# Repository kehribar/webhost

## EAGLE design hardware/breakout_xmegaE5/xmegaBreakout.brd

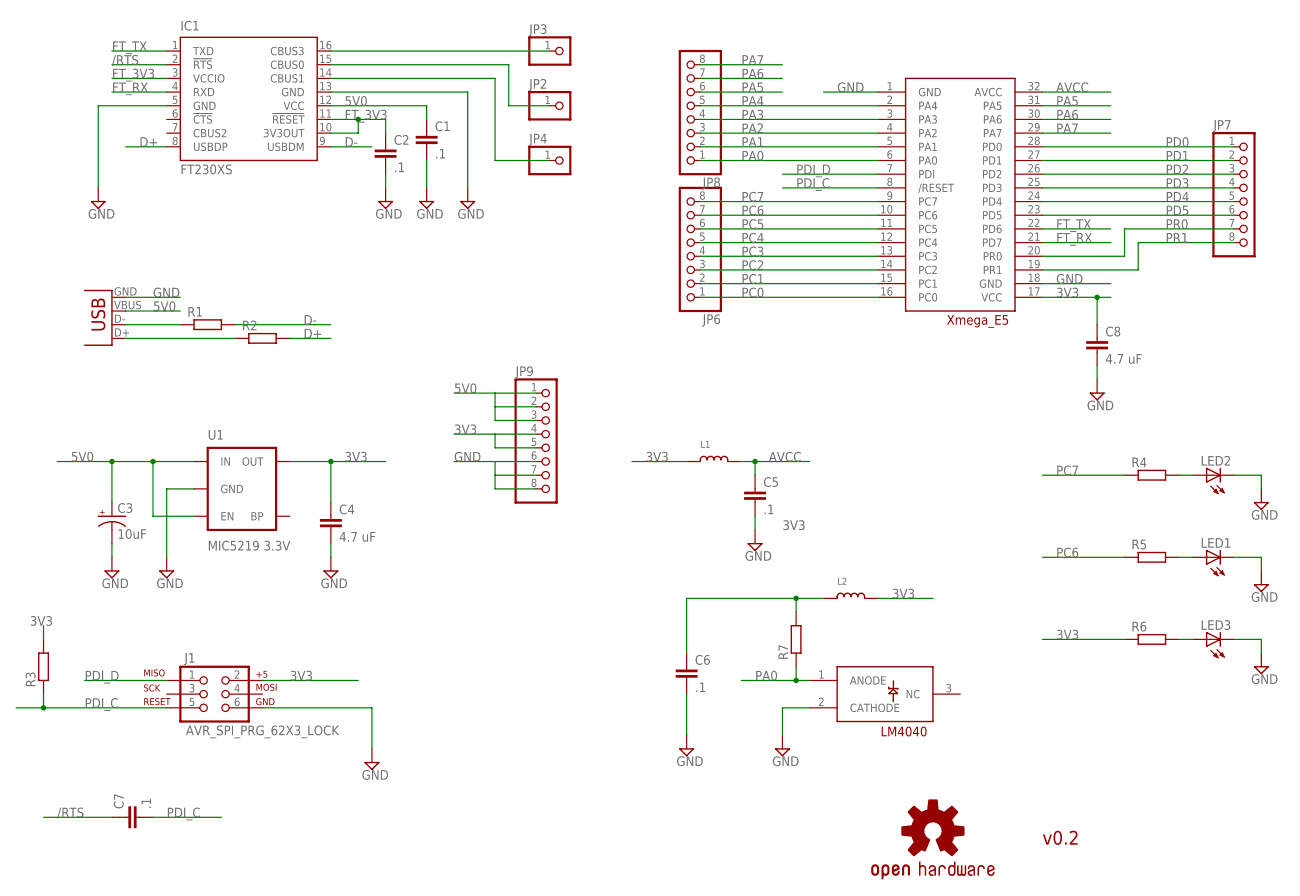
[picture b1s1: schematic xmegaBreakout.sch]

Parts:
C1, C2, C5, C6, C7: .1; C0603
C3: 10uF; EIA3216
C4, C8: 4.7 uF; C0603
IC1: FT230XS; SSOP16
J1: AVR_SPI_PRG_62X3_LOCK; 2X3_LOCK
JP1: USBOLD; USB-MINIB-OLD
JP2, JP3, JP4: HEADER-1X1ROUND; 1X01_ROUND
JP6, JP7, JP8, JP9: HEADER-1X8ROUND; 1X08_ROUND
L1, L2: INDUCTOR0805; 0805
LED1, LED2, LED3: LED0603; LED-0603
LOGO1: OSHW-LOGOS; OSHW-LOGO-S
R1, R2, R3, R4, R5, R6, R7: R-EU_R0603; R0603
U1: MIC5219 3.3V; SOT23-5
U$1: IHSAN_XMEGA_E5; TQFP32-08
U$2: IHSAN_LM4040; SOT23-3

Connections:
3V3: C4.1, C8.1, J1.2, JP9.4, JP9.5, L1.1, L2.2, R3.2, R6.1, U1.5 (OUT), U$1.17 (VCC)
5V0: C1.1, C3.A (+), IC1.12 (VCC), JP1.VBUS, JP9.1, JP9.2, JP9.3, U1.1 (IN), U1.3 (EN)
/RTS: C7.1, IC1.2 (!RTS)
AVCC: C5.1, L1.2, U$1.32 (AVCC)
D+: IC1.8 (USBDP), R2.2
D-: IC1.9 (USBDM), R1.2
FT_3V3: C2.1, IC1.3 (VCCIO), IC1.10 (3V3OUT), IC1.11 (!RESET)
FT_RX: IC1.4 (RXD), U$1.21 (PD7)
FT_TX: IC1.1 (TXD), U$1.22 (PD6)
GND: C1.2, C2.2, C3.C (-), C4.2, C5.2, C6.2, C8.2, IC1.5 (GND), IC1.13 (GND), J1.6, JP1.GND, JP9.6, JP9.7, JP9.8, LED1.C, LED2.C, LED3.C, U1.2 (GND), U$1.1 (GND), U$1.18 (GND), U$2.2 (CATHODE)
unnamed: JP1.D-, R1.1
unnamed: JP1.D+, R2.1
unnamed: LED2.A, R4.2
unnamed: LED1.A, R5.2
unnamed: IC1.16 (CBUS3), JP3.1
unnamed: IC1.15 (CBUS0), JP2.1
unnamed: IC1.14 (CBUS1), JP4.1
unnamed: LED3.A, R6.2
unnamed: C6.1, L2.1, R7.2
PA0: JP8.1, R7.1, U$1.6 (PA0), U$2.1 (ANODE)
PA1: JP8.2, U$1.5 (PA1)
PA2: JP8.3, U$1.4 (PA2)
PA3: JP8.4, U$1.3 (PA3)
PA4: JP8.5, U$1.2 (PA4)
PA5: JP8.6, U$1.31 (PA5)
PA6: JP8.7, U$1.30 (PA6)
PA7: JP8.8, U$1.29 (PA7)
PC0: JP6.1, U$1.16 (PC0)
PC1: JP6.2, U$1.15 (PC1)
PC2: JP6.3, U$1.14 (PC2)
PC3: JP6.4, U$1.13 (PC3)
PC4: JP6.5, U$1.12 (PC4)
PC5: JP6.6, U$1.11 (PC5)
PC6: JP6.7, R5.1, U$1.10 (PC6)
PC7: JP6.8, R4.1, U$1.9 (PC7)
PD0: JP7.1, U$1.28 (PD0)
PD1: JP7.2, U$1.27 (PD1)
PD2: JP7.3, U$1.26 (PD2)
PD3: JP7.4, U$1.25 (PD3)
PD4: JP7.5, U$1.24 (PD4)
PD5: JP7.6, U$1.23 (PD5)
PDI_C: C7.2, J1.5, R3.1, U$1.8 (/RESET)
PDI_D: J1.1, U$1.7 (PDI)
PR0: JP7.7, U$1.20 (PR0)
PR1: JP7.8, U$1.19 (PR1)

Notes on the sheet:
v0.2

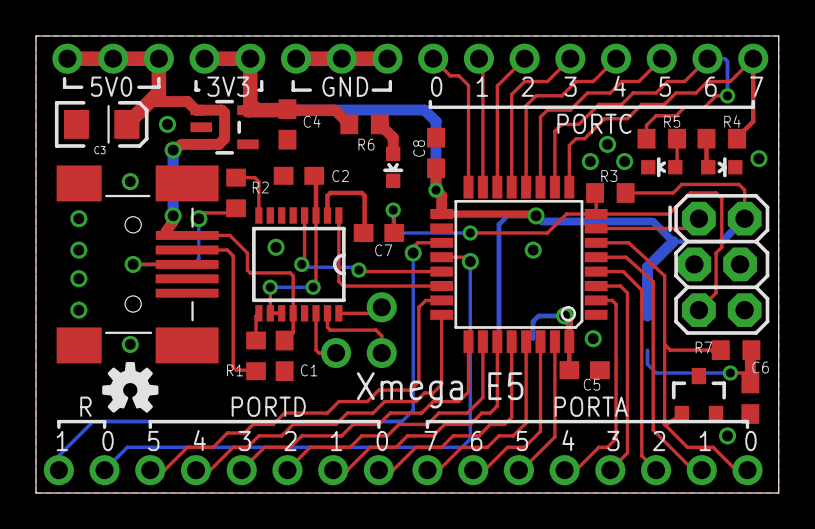
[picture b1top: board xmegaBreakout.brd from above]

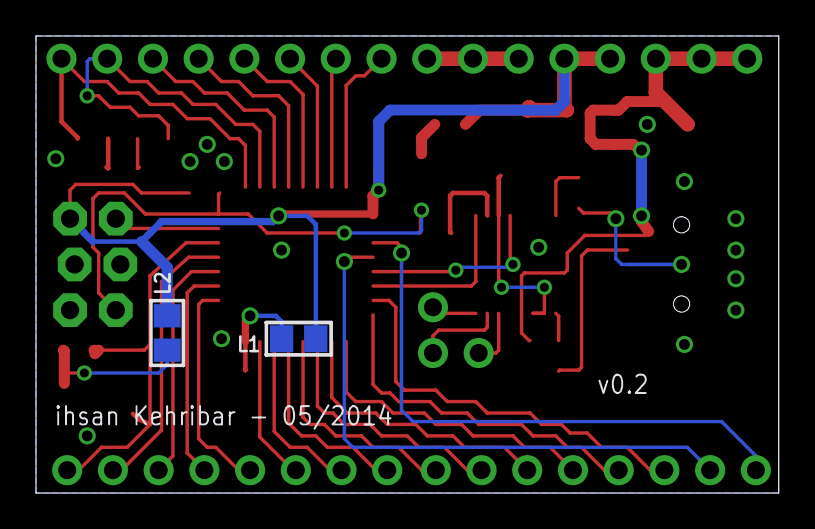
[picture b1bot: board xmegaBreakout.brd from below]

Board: 2 copper layers, 41.3 x 25.4 mm, 34 parts (2 on the bottom side), 45 nets.

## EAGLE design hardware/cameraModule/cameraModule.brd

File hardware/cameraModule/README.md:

Embedded camera module
================

This was my attempt to create a breakout board for the 10$ CMOS camera chip (TCM8230MD) that Sparkfun sells: [https://www.sparkfun.com/products/8667 ](https://www.sparkfun.com/products/8667)

Footprint for the camera and initial schematic file is coming from this blog post: [http://www.ikalogic.com/image-processing-as-a-sensor/](http://www.ikalogic.com/image-processing-as-a-sensor/)

I've populated this board but never actually managed to get an image out of it ...

### Schematic

### Layout

### Build

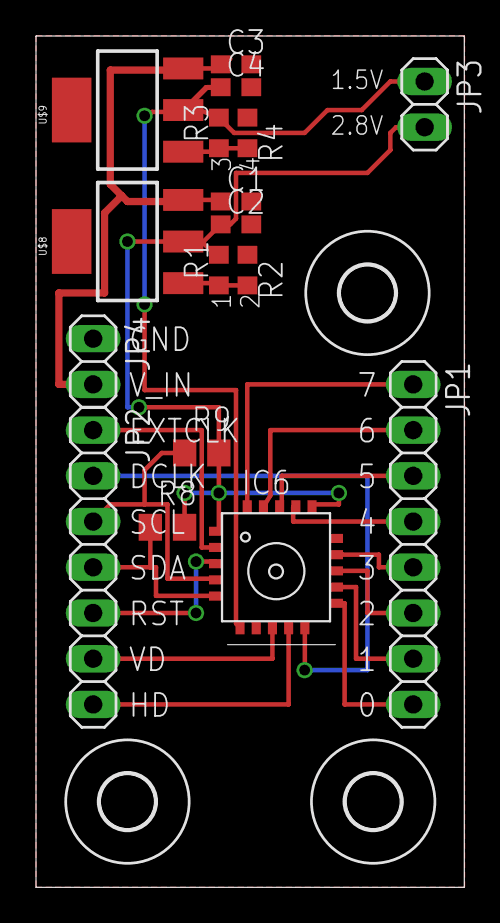
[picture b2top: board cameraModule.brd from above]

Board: 2 copper layers, 23.8 x 47.3 mm, 20 parts (0 on the bottom side), 21 nets.

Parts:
C1, C2, C3, C4: C0603
IC6: TCM8230MDA; TCM8230MD
JP1: 1X08
JP2: 1X07
JP3, JP4: 1X02
R1, R2, R3, R4: R0603
R8, R9: 1K5; R0805
U$4, U$5, U$7: 3,0
U$8, U$9: V_REG_317SMD; SOT223

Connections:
1.8V: C4.1, IC6.6, JP3.1, R3.2, U$9.2
2.8V: C2.1, IC6.1, IC6.16, JP3.2, R1.2, R8.2, R9.2, U$8.2
CAM_BUS0: IC6.11, JP1.8
CAM_BUS1: IC6.12, JP1.7
CAM_BUS2: IC6.13, JP1.6
CAM_BUS3: IC6.14, JP1.5
CAM_BUS4: IC6.17, JP1.4
CAM_BUS5: IC6.18, JP1.3
CAM_BUS6: IC6.19, JP1.2
CAM_BUS7: IC6.20, JP1.1
DCLK: IC6.10, JP2.2
EXTCLK: IC6.2, JP2.1
GND: C1.2, C2.2, C3.2, C4.2, IC6.7, IC6.15, JP4.1, R2.1, R4.1
HD: IC6.9, JP2.7
unnamed: R1.1, R2.2, U$8.1
unnamed: R3.1, R4.2, U$9.1
RST: IC6.3, JP2.5
SCL: IC6.4, JP2.3, R9.1
SDA: IC6.5, JP2.4, R8.1
VD: IC6.8, JP2.6
V_IN: C1.1, C3.1, JP4.2, U$8.3, U$9.3

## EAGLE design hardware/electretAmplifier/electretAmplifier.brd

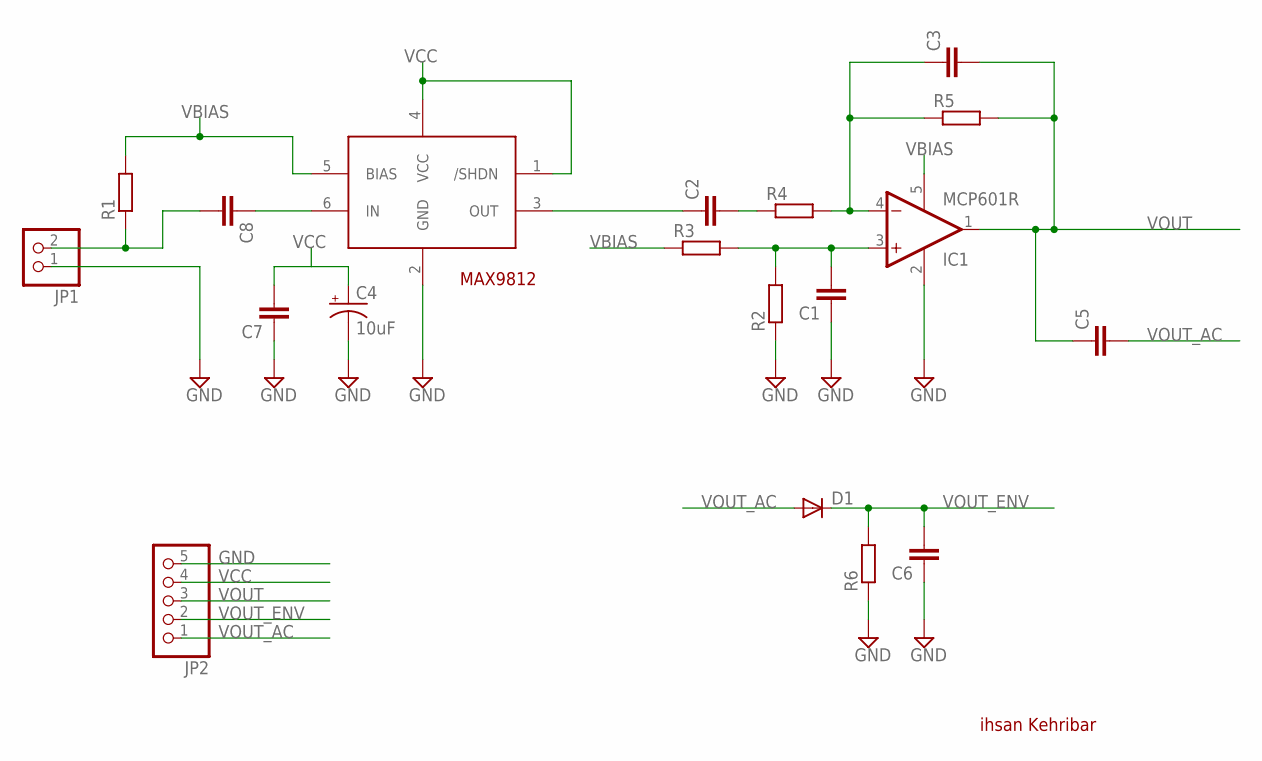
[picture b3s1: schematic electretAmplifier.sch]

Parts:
C1, C2, C3, C5, C6, C7, C8: C-EUC0603; C0603
C4: 10uF; EIA3216
D1: DIODESOD; SOD-323
IC1: MCP601R; SOT23-5
JP1: HEADER-1X2ROUND; 1X02_ROUND
JP2: HEADER-1X5ROUND; 1X05_ROUND
R1, R2, R3, R4, R5, R6: R-EU_R0603; R0603
U$1: IHSAN_MAX9812; SC70-6

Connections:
GND: C1.1, C4.C (-), C6.1, C7.1, IC1.2 (V+), JP1.1, JP2.5, R2.1, R6.1, U$1.2 (GND)
unnamed: C3.1, IC1.4 (-IN), R4.2, R5.1
unnamed: C8.2, JP1.2, R1.1
unnamed: C1.2, IC1.3 (+IN), R2.2, R3.2
unnamed: C2.2, R4.1
unnamed: C2.1, U$1.3 (OUT)
unnamed: C8.1, U$1.6 (IN)
VBIAS: IC1.5 (V-), R1.2, R3.1, U$1.5 (BIAS)
VCC: C4.A (+), C7.2, JP2.4, U$1.1 (/SHDN), U$1.4 (VCC)
VOUT: C3.2, C5.1, IC1.1 (OUT), JP2.3, R5.2
VOUT_AC: C5.2, D1.2 (A), JP2.1
VOUT_ENV: C6.2, D1.1 (C), JP2.2, R6.2

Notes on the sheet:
ihsan Kehribar

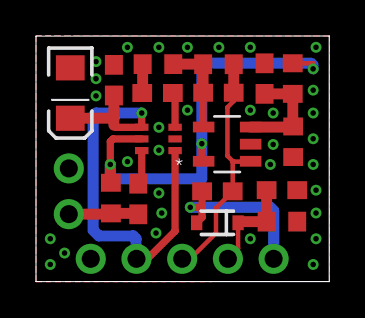
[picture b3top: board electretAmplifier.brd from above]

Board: 2 copper layers, 16.3 x 13.6 mm, 19 parts (0 on the bottom side), 12 nets.

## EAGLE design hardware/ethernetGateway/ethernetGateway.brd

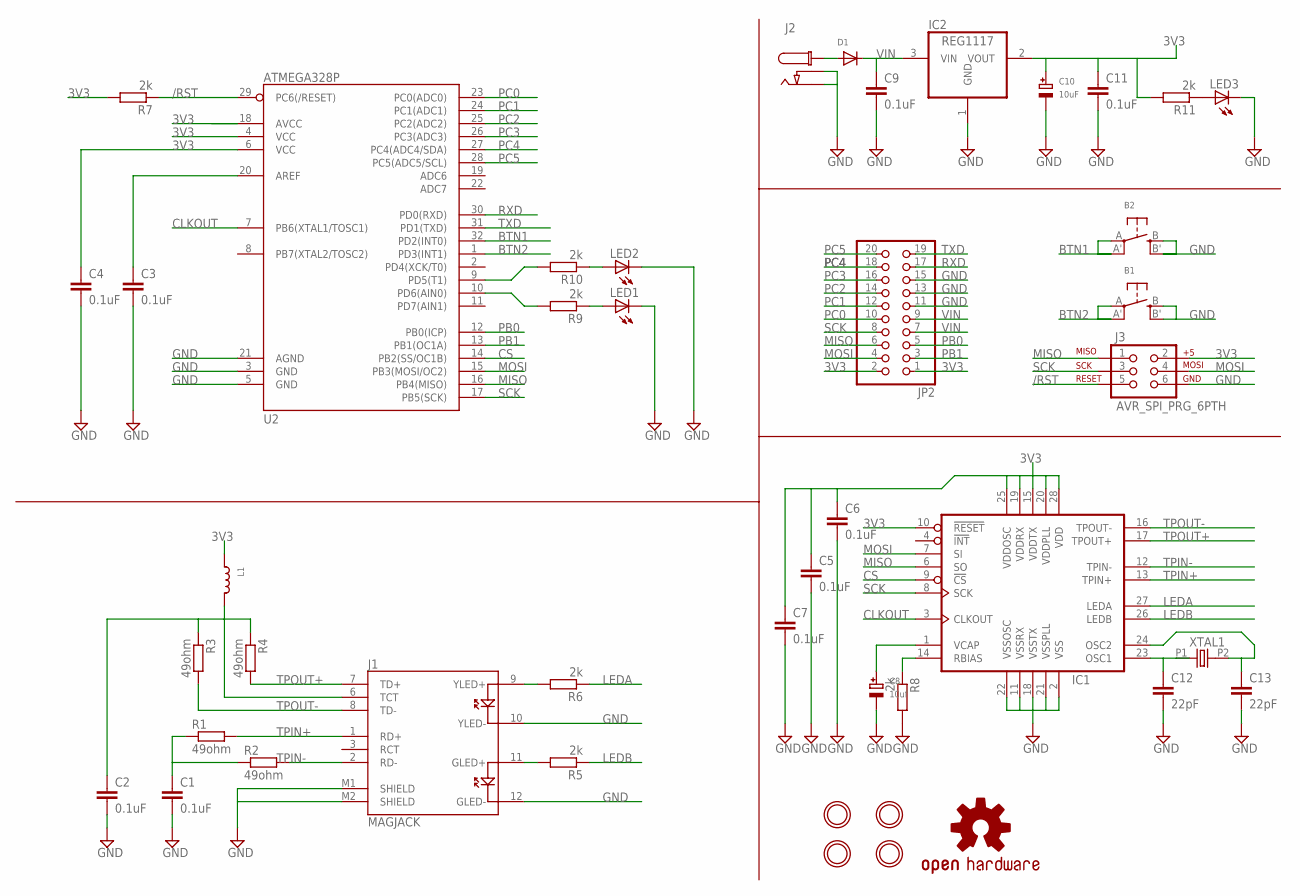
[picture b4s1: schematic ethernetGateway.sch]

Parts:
B1, B2: SWITCH_TACT_SMT4.6X2.8; BTN_KMR2_4.6X2.8
C1, C2, C3, C4, C5, C6, C7, C9, C11: 0.1uF; C0805
C8: 10uf; EIA3528-21/B-W
C10: 10uF; EIA3528-21/B-W
C12, C13: 22pF; C0805
D1: DIODEDO-1N4148; DO-1N4148
IC1: IC_ENC28J60-SOIC-28; SOIC-28W
IC2: REG1117; SOT223
J1: MAGJACK
J2: CON_DC_M-DC_PTH; DC_BARREL_JACK_PTH_2MM
J3: AVR_SPI_PRG_6PTH; 2X3
JP2: PINHD-2X10; 2X10
L1: INDUCTOR0805; 0805
LED1, LED2, LED3: LED-0805; LED-805
LOGO1: OSHW-LOGOL; OSHW-LOGO-L
R1, R2, R3, R4: 49ohm; R0805
R5, R6, R7, R8, R9, R10, R11: 2k; R0805
U2: ATMEGA328P; TQFP32-08
U$1, U$2, U$3, U$4: MOUNTINGHOLE2.0; MOUNTINGHOLE_2.0_PLATED
XTAL1: OSC-XTAL-HC-49U-PTH; HC-49U-PTH

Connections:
3V3: C4.1, C5.1, C6.1, C7.1, C10.+, C11.1, IC1.10 (!RESET), IC1.15 (VDDTX), IC1.19 (VDDRX), IC1.20 (VDDPLL), IC1.25 (VDDOSC), IC1.28 (VDD), IC2.2 (VOUT), J3.2, JP2.1, JP2.2, L1.1, R7.2, R11.2, U2.4 (VCC), U2.6 (VCC), U2.18 (AVCC)
/RST: J3.5, R7.1, U2.29 (PC6(/RESET))
BTN1: B2.A, B2.A' (P1), U2.32 (PD2(INT0))
BTN2: B1.A, B1.A' (P1), U2.1 (PD3(INT1))
CLKOUT: IC1.3 (CLKOUT), U2.7 (PB6(XTAL1/TOSC1))
CS: IC1.9 (!CS), U2.14 (PB2(SS/OC1B))
GND: B1.B (S), B1.B' (S1), B2.B (S), B2.B' (S1), C1.2, C2.2, C3.2, C4.2, C5.2, C6.2, C7.2, C8.-, C9.2, C10.-, C11.2, C12.2, C13.2, IC1.2 (VSS), IC1.11 (VSSRX), IC1.18 (VSSTX), IC1.21 (VSSPLL), IC1.22 (VSSOSC), IC2.1 (GND), J1.10 (YLED-), J1.12 (GLED-), J1.M1 (SHIELD), J1.M2 (SHIELD), J2.P2 (P3), J2.P3 (P2), J3.6, JP2.11, JP2.13, JP2.15, LED1.C, LED2.C, LED3.C, R8.2, U2.3 (GND), U2.5 (GND), U2.21 (AGND)
LEDA: IC1.27 (LEDA), R6.1
LEDB: IC1.26 (LEDB), R5.1
MISO: IC1.6 (SO), J3.1, JP2.6, U2.16 (PB4(MISO))
MOSI: IC1.7 (SI), J3.4, JP2.4, U2.15 (PB3(MOSI/OC2))
unnamed: C1.1, R1.1, R2.1
unnamed: J1.9 (YLED+), R6.2
unnamed: C13.1, IC1.24 (OSC2), XTAL1.P2 (2)
unnamed: J1.11 (GLED+), R5.2
unnamed: C12.1, IC1.23 (OSC1), XTAL1.P1 (1)
unnamed: C2.1, J1.6 (TCT), L1.2, R3.1, R4.1
unnamed: C8.+, IC1.1 (VCAP)
unnamed: C3.1, U2.20 (AREF)
unnamed: IC1.14 (RBIAS), R8.1
unnamed: LED1.A, R9.1
unnamed: LED2.A, R10.1
unnamed: D1.A, J2.P1
unnamed: R10.2, U2.9 (PD5(T1))
unnamed: R9.2, U2.10 (PD6(AIN0))
unnamed: LED3.A, R11.1
PB0: JP2.5, U2.12 (PB0(ICP))
PB1: JP2.3, U2.13 (PB1(OC1A))
PC0: JP2.10, U2.23 (PC0(ADC0))
PC1: JP2.12, U2.24 (PC1(ADC1))
PC2: JP2.14, U2.25 (PC2(ADC2))
PC3: JP2.16, U2.26 (PC3(ADC3))
PC4: JP2.18, U2.27 (PC4(ADC4/SDA))
PC5: JP2.20, U2.28 (PC5(ADC5/SCL))
RXD: JP2.17, U2.30 (PD0(RXD))
SCK: IC1.8 (SCK), J3.3, JP2.8, U2.17 (PB5(SCK))
TPIN+: IC1.13 (TPIN+), J1.1 (RD+), R1.2
TPIN-: IC1.12 (TPIN-), J1.2 (RD-), R2.2
TPOUT+: IC1.17 (TPOUT+), J1.7 (TD+), R4.2
TPOUT-: IC1.16 (TPOUT-), J1.8 (TD-), R3.2
TXD: JP2.19, U2.31 (PD1(TXD))
VIN: C9.1, D1.C, IC2.3 (VIN), JP2.7, JP2.9

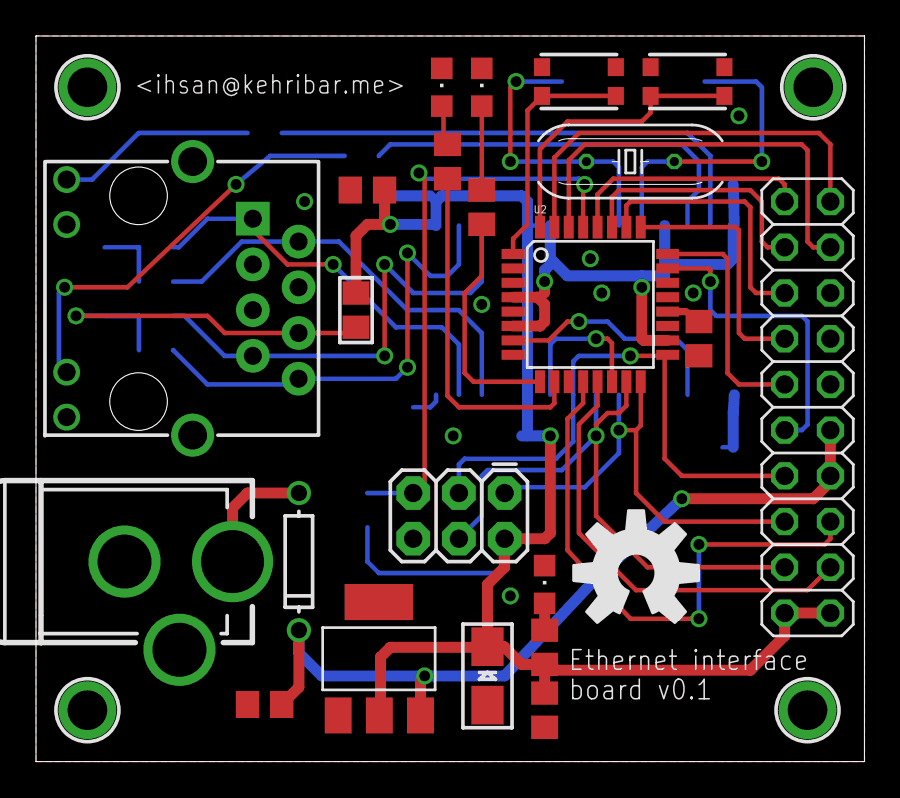
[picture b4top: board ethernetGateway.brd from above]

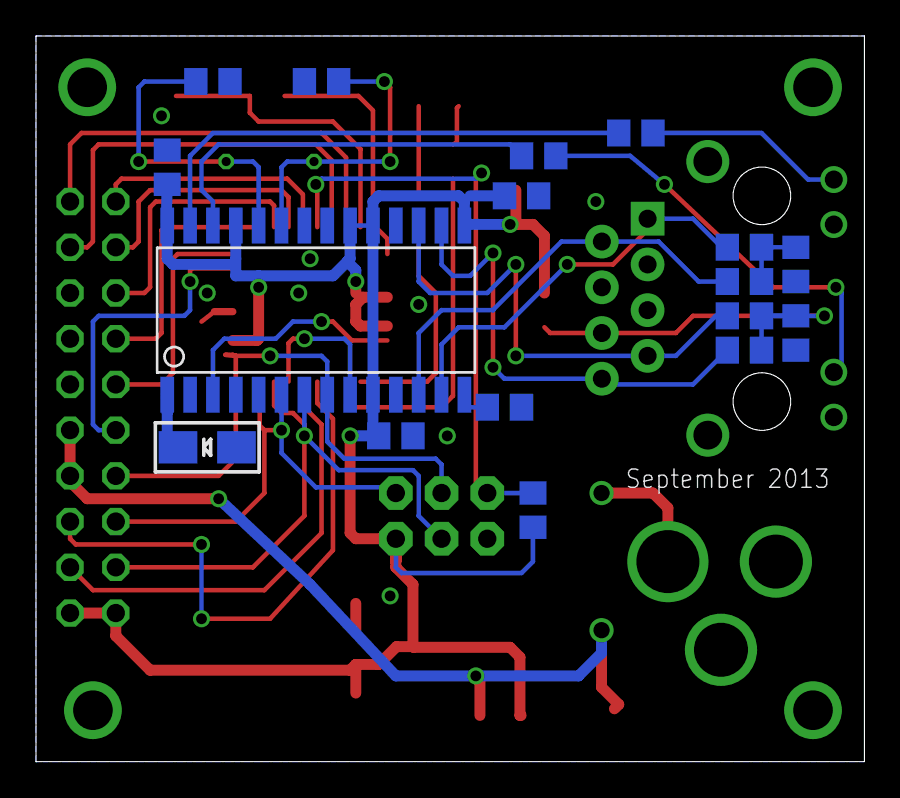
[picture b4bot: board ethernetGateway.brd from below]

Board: 2 copper layers, 46.0 x 40.3 mm, 44 parts (17 on the bottom side), 42 nets.

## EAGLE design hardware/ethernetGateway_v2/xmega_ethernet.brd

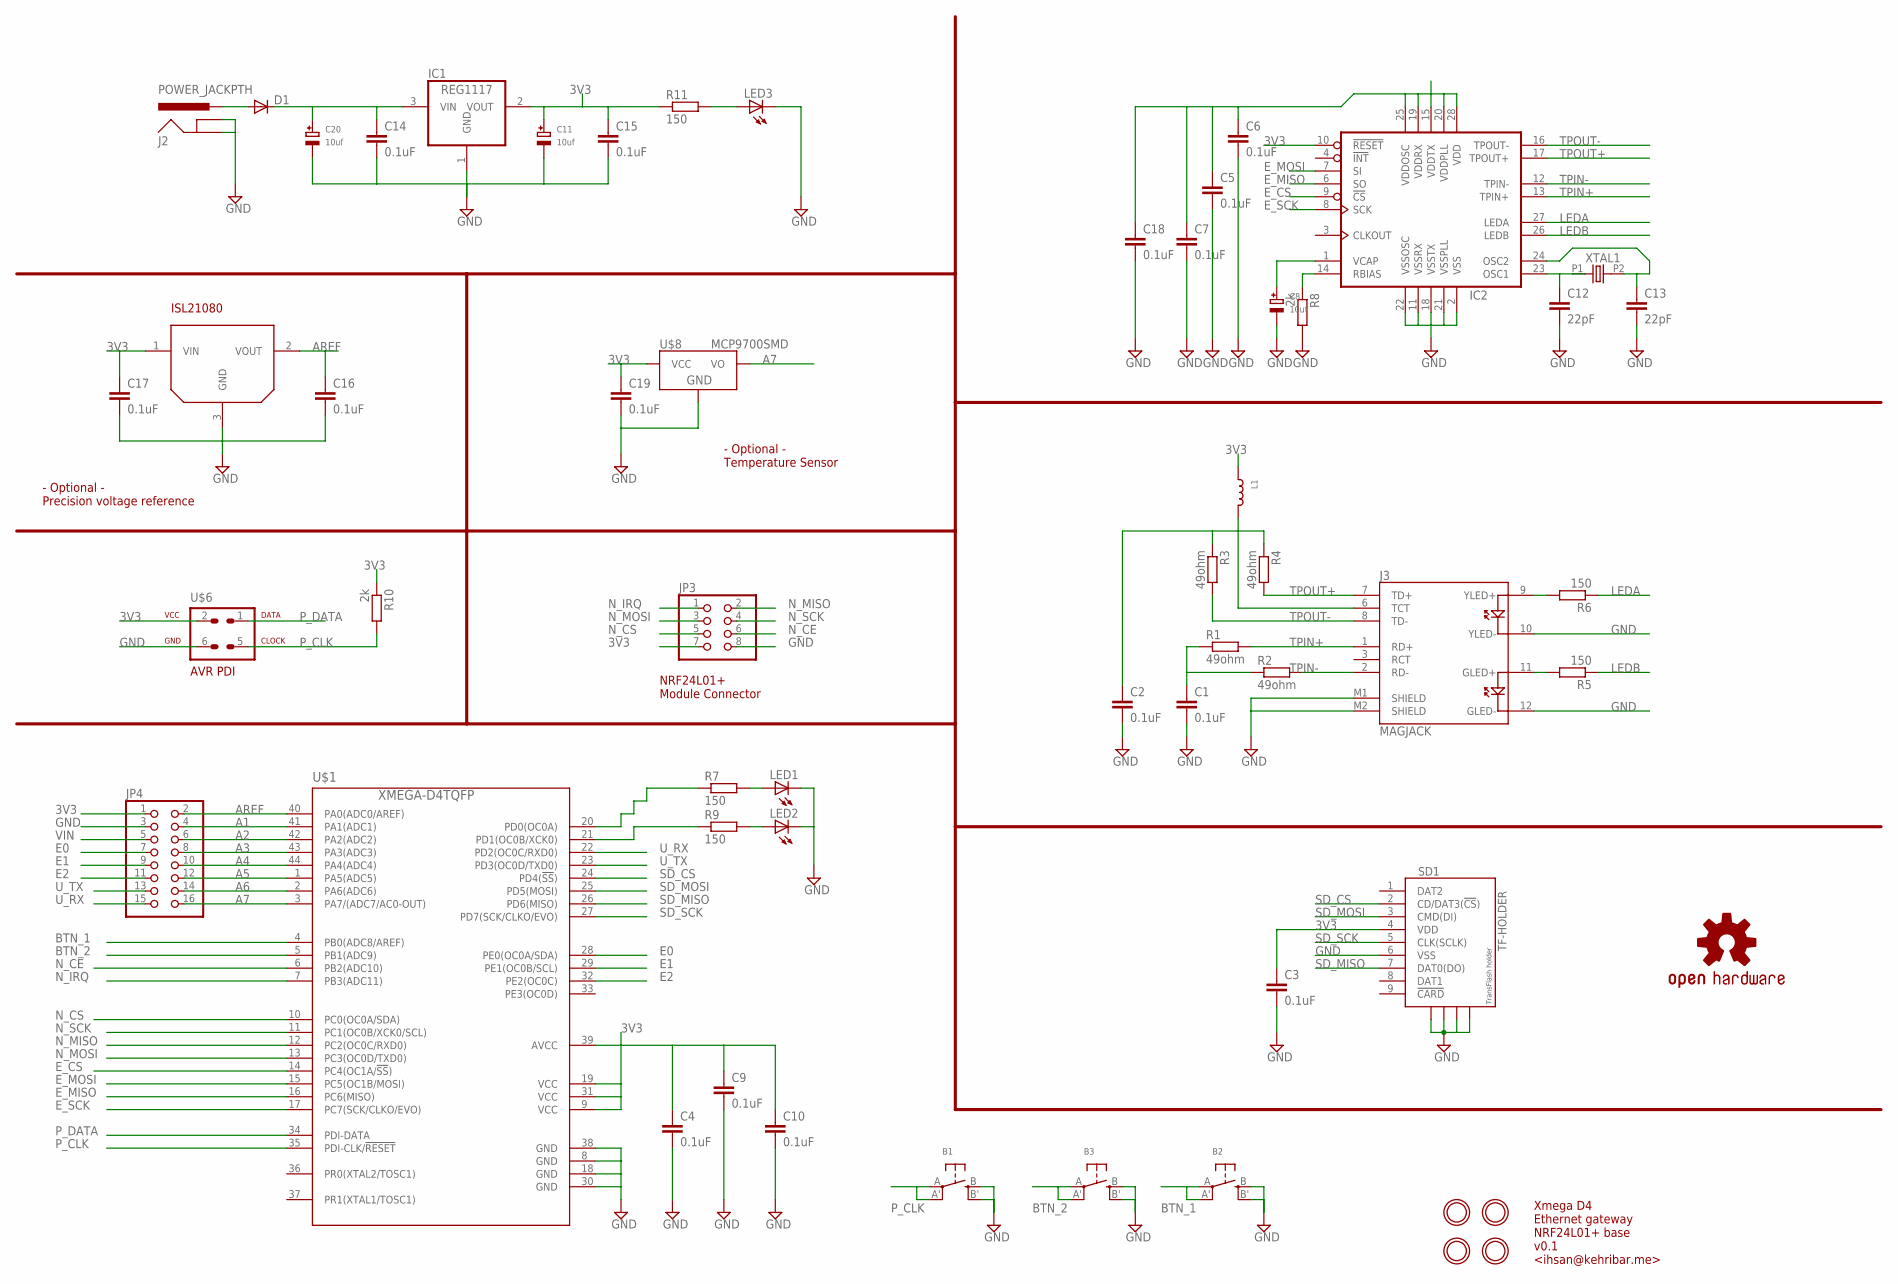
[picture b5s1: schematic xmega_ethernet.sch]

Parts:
B1, B2, B3: SWITCH_TACT_SMT4.6X2.8; BTN_KMR2_4.6X2.8
C1, C2, C3, C4, C5, C6, C7, C9, C10, C14, C15, C16, C17, C18, C19: 0.1uF; C0805
C8, C11, C20: 10uf; EIA3528-21/B-W
C12, C13: 22pF; C0805
D1: DIODE1N4148; DIODE-1N4148
IC1: REG1117; SOT223
IC2: IC_ENC28J60-SOIC-28; SOIC-28W
J2: POWER_JACKPTH; POWER_JACK_PTH
J3: MAGJACK
JP3: PINHD-2X4; 2X04
JP4: PINHD-2X8; 2X08
L1: INDUCTOR0805; 0805
LED1, LED2, LED3: LED-0805; LED-805
LOGO1: OSHW-LOGOM; OSHW-LOGO-M
R1, R2, R3, R4: 49ohm; R0805
R5, R6, R7, R9, R11: 150; R0805
R8, R10: 2k; R0805
SD1: TF-HOLDER; TF-PULL
U$1: XMEGA-D4TQFP; TQFP44
U$2, U$3, U$4, U$5: MOUNTINGHOLE3.0THIN; MOUNTINGHOLE_3.0_PLATEDTHIN
U$6: AVR-PDIVERT; AVR-ISP-6
U$7: IHSAN_ISL21080; SOT23-3
U$8: MCP9700SMD; SOT23-3
XTAL1: OSC-XTAL-HC-49U-PTH; HC-49U-PTH

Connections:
3V3: C3.1, C4.1, C5.1, C6.1, C7.1, C9.1, C10.1, C11.+, C15.1, C17.1, C18.1, C19.1, IC1.2 (VOUT), IC2.10 (!RESET), IC2.15 (VDDTX), IC2.19 (VDDRX), IC2.20 (VDDPLL), IC2.25 (VDDOSC), IC2.28 (VDD), JP3.7, JP4.1, L1.1, R10.1, R11.1, SD1.4 (VDD), U$1.9 (VCC), U$1.19 (VCC), U$1.31 (VCC), U$1.39 (AVCC), U$6.2, U$7.1 (VIN), U$8.1 (VCC)
A1: JP4.4, U$1.41 (PA1(ADC1))
A2: JP4.6, U$1.42 (PA2(ADC2))
A3: JP4.8, U$1.43 (PA3(ADC3))
A4: JP4.10, U$1.44 (PA4(ADC4))
A5: JP4.12, U$1.1 (PA5(ADC5))
A6: JP4.14, U$1.2 (PA6(ADC6))
A7: JP4.16, U$1.3 (PA7/(ADC7/AC0-OUT)), U$8.2 (VO)
AREF: C16.1, JP4.2, U$1.40 (PA0(ADC0/AREF)), U$7.2 (VOUT)
BTN_1: B2.A, B2.A' (P1), U$1.4 (PB0(ADC8/AREF))
BTN_2: B3.A, B3.A' (P1), U$1.5 (PB1(ADC9))
E0: JP4.7, U$1.28 (PE0(OC0A/SDA))
E1: JP4.9, U$1.29 (PE1(OC0B/SCL))
E2: JP4.11, U$1.32 (PE2(OC0C))
E_CS: IC2.9 (!CS), U$1.14 (PC4(OC1A/!SS!))
E_MISO: IC2.6 (SO), U$1.16 (PC6(MISO))
E_MOSI: IC2.7 (SI), U$1.15 (PC5(OC1B/MOSI))
E_SCK: IC2.8 (SCK), U$1.17 (PC7(SCK/CLKO/EVO))
GND: B1.B (S), B1.B' (S1), B2.B (S), B2.B' (S1), B3.B (S), B3.B' (S1), C1.2, C2.2, C3.2, C4.2, C5.2, C6.2, C7.2, C8.-, C9.2, C10.2, C11.-, C12.2, C13.2, C14.2, C15.2, C16.2, C17.2, C18.2, C19.2, C20.-, IC1.1 (GND), IC2.2 (VSS), IC2.11 (VSSRX), IC2.18 (VSSTX), IC2.21 (VSSPLL), IC2.22 (VSSOSC), J2.GND, J2.GNDBREAK, J3.10 (YLED-), J3.12 (GLED-), J3.M1 (SHIELD), J3.M2 (SHIELD), JP3.8, JP4.3, LED1.C, LED2.C, LED3.C, R8.2, SD1.6 (VSS), SD1.S1, SD1.S2, SD1.S3, SD1.S4, U$1.8 (GND), U$1.18 (GND), U$1.30 (GND), U$1.38 (GND), U$6.6, U$7.3 (GND), U$8.3 (GND)
LEDA: IC2.27 (LEDA), R6.1
LEDB: IC2.26 (LEDB), R5.1
unnamed: C1.1, R1.1, R2.1
unnamed: J3.9 (YLED+), R6.2
unnamed: C13.1, IC2.24 (OSC2), XTAL1.P2 (2)
unnamed: J3.11 (GLED+), R5.2
unnamed: C12.1, IC2.23 (OSC1), XTAL1.P1 (1)
unnamed: C2.1, J3.6 (TCT), L1.2, R3.1, R4.1
unnamed: C8.+, IC2.1 (VCAP)
unnamed: IC2.14 (RBIAS), R8.1
unnamed: R7.1, U$1.20 (PD0(OC0A))
unnamed: R9.1, U$1.21 (PD1(OC0B/XCK0))
unnamed: LED1.A, R7.2
unnamed: LED2.A, R9.2
unnamed: D1.A, J2.PWR
unnamed: LED3.A, R11.2
N_CE: JP3.6, U$1.6 (PB2(ADC10))
N_CS: JP3.5, U$1.10 (PC0(OC0A/SDA))
N_IRQ: JP3.1, U$1.7 (PB3(ADC11))
N_MISO: JP3.2, U$1.12 (PC2(OC0C/RXD0))
N_MOSI: JP3.3, U$1.13 (PC3(OC0D/TXD0))
N_SCK: JP3.4, U$1.11 (PC1(OC0B/XCK0/SCL))
P_CLK: B1.A, B1.A' (P1), R10.2, U$1.35 (PDI-CLK/!RESET), U$6.5
P_DATA: U$1.34 (PDI-DATA), U$6.1
SD_CS: SD1.2 (CD/DAT3(!CS!)), U$1.24 (PD4(!SS!))
SD_MISO: SD1.7 (DAT0(DO)), U$1.26 (PD6(MISO))
SD_MOSI: SD1.3 (CMD(DI)), U$1.25 (PD5(MOSI))
SD_SCK: SD1.5 (CLK(SCLK)), U$1.27 (PD7(SCK/CLKO/EVO))
TPIN+: IC2.13 (TPIN+), J3.1 (RD+), R1.2
TPIN-: IC2.12 (TPIN-), J3.2 (RD-), R2.2
TPOUT+: IC2.17 (TPOUT+), J3.7 (TD+), R4.2
TPOUT-: IC2.16 (TPOUT-), J3.8 (TD-), R3.2
U_RX: JP4.15, U$1.22 (PD2(OC0C/RXD0))
U_TX: JP4.13, U$1.23 (PD3(OC0D/TXD0))
VIN: C14.1, C20.+, D1.C, IC1.3 (VIN), JP4.5

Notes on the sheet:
NRF24L01+ Module Connector
- Optional - Temperature Sensor
- Optional - Precision voltage reference
Xmega D4 Ethernet gateway NRF24L01+ base v0.1 <ihsan@kehribar.me>

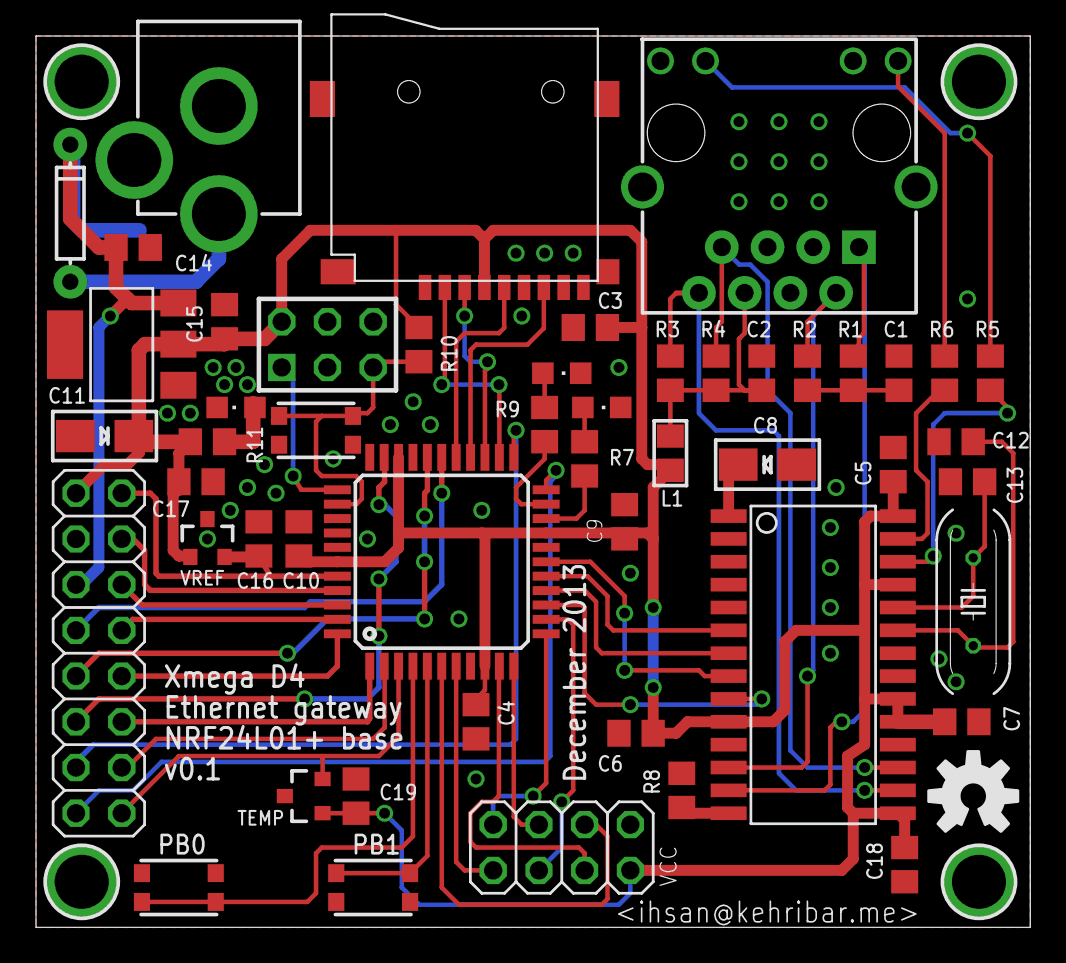
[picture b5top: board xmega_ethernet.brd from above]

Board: 2 copper layers, 55.2 x 49.5 mm, 56 parts (1 on the bottom side), 54 nets.

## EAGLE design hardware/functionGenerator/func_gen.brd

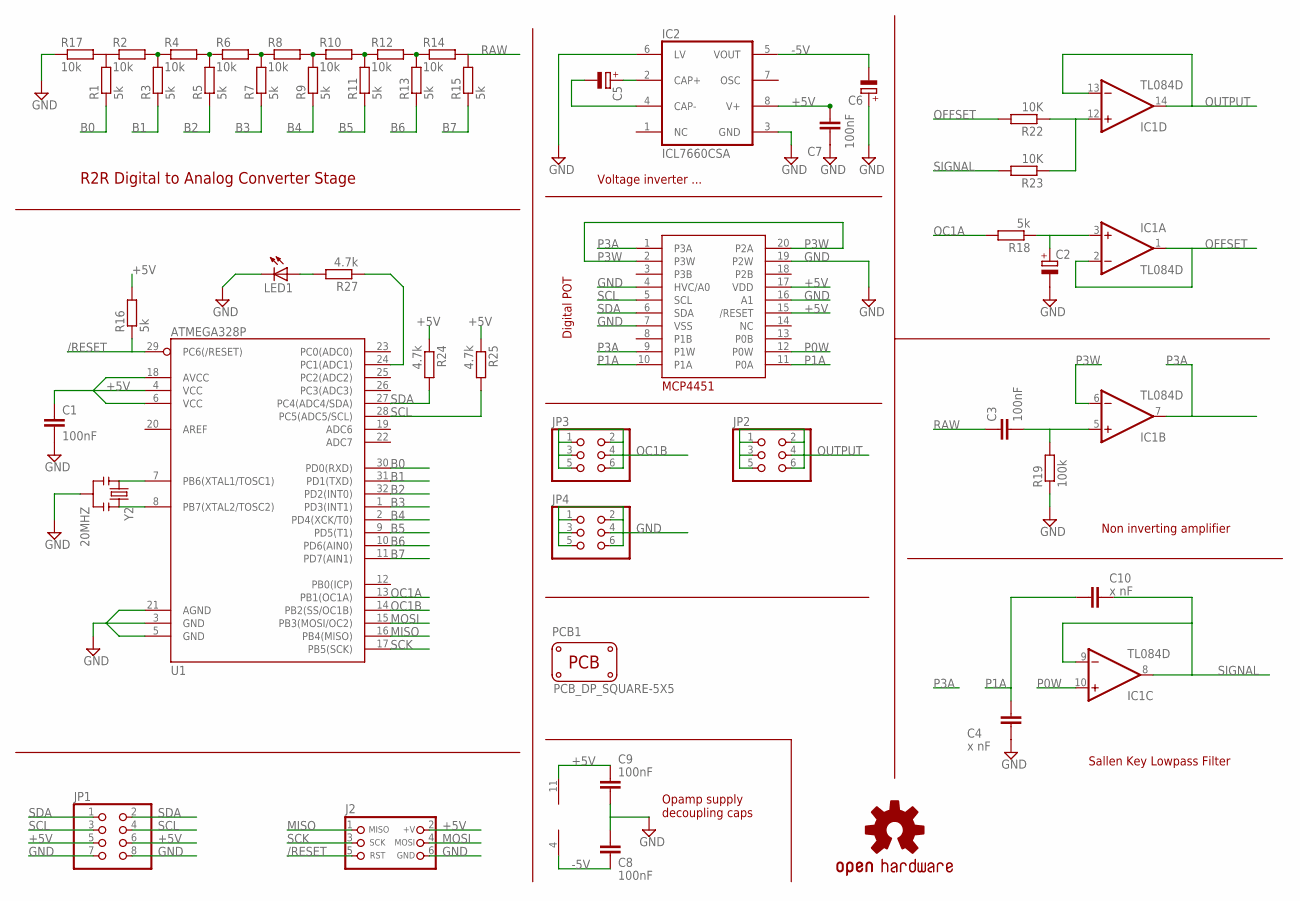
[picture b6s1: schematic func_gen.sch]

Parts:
C1, C3, C7, C8, C9: 100nF; C0603
C2, C5, C6: CPOL-EUE5-5; E5-5
C4, C10: x nF; C0603
IC1: TL084D; SO14
IC2: ICL7660CSA; SO08
J2: CON_HEADER_PRG_AVR_ICSP; HEADER_PRG_2X03
JP1: PINHD-2X4; 2X04
JP2, JP3, JP4: PINHD-2X3; 2X03
LED1: LED-0805; LED-805
LOGO1: OSHW-LOGOM; OSHW-LOGO-M
PCB1: PCB_DP_SQUARE-5X5; DP5050_V1
R1, R3, R5, R7, R9, R11, R13, R15, R16, R18: 5k; R0603
R2, R4, R6, R8, R10, R12, R14, R17: 10k; R0603
R19: 100k; R0603
R22, R23: 10K; R0603
R24, R25, R27: 4.7k; R0603
U1: ATMEGA328P; TQFP32-08
U$1: IHSAN_MCP4451DOGRU; TSSOP20
Y2: 20MHZ; RESONATOR-PTH

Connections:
+5V: C1.1, C7.2, C9.2, IC1.11 (V-), IC2.8 (V+), J2.2 (+V), JP1.5, JP1.6, R16.2, R24.1, R25.1, U1.4 (VCC), U1.6 (VCC), U1.18 (AVCC), U$1.15 (/RESET), U$1.17 (VDD)
-5V: C6.-, C8.1, IC1.4 (V+), IC2.5 (VOUT)
/RESET: J2.5 (RST), R16.1, U1.29 (PC6(/RESET))
B0: R1.1, U1.30 (PD0(RXD))
B1: R3.1, U1.31 (PD1(TXD))
B2: R5.1, U1.32 (PD2(INT0))
B3: R7.1, U1.1 (PD3(INT1))
B4: R9.1, U1.2 (PD4(XCK/T0))
B5: R11.1, U1.9 (PD5(T1))
B6: R13.1, U1.10 (PD6(AIN0))
B7: R15.1, U1.11 (PD7(AIN1))
GND: C1.2, C2.-, C4.1, C6.+, C7.1, C8.2, C9.1, IC2.3 (GND), IC2.6 (LV), J2.6 (GND), JP1.7, JP1.8, JP4.1, JP4.2, JP4.3, JP4.4, JP4.5, JP4.6, LED1.C, R17.1, R19.1, U1.3 (GND), U1.5 (GND), U1.21 (AGND), U$1.4 (HVC/A0), U$1.7 (VSS), U$1.16 (A1), U$1.19 (P2W), Y2.2
MISO: J2.1 (MISO), U1.16 (PB4(MISO))
MOSI: J2.4 (MOSI), U1.15 (PB3(MOSI/OC2))
unnamed: R1.2, R2.1, R17.2
unnamed: R2.2, R3.2, R4.1
unnamed: R4.2, R5.2, R6.1
unnamed: R6.2, R7.2, R8.1
unnamed: R8.2, R9.2, R10.1
unnamed: R10.2, R11.2, R12.1
unnamed: R12.2, R13.2, R14.1
unnamed: U1.8 (PB7(XTAL2/TOSC2)), Y2.3
unnamed: U1.7 (PB6(XTAL1/TOSC1)), Y2.1
unnamed: C2.+, IC1.3 (+IN), R18.1
unnamed: C3.2, IC1.5 (+IN), R19.2
unnamed: C5.+, IC2.2 (CAP+)
unnamed: C5.-, IC2.4 (CAP-)
unnamed: IC1.12 (+IN), R22.1, R23.1
unnamed: R27.1, U1.24 (PC1(ADC1))
unnamed: LED1.A, R27.2
OC1A: R18.2, U1.13 (PB1(OC1A))
OC1B: JP3.1, JP3.2, JP3.3, JP3.4, JP3.5, JP3.6, U1.14 (PB2(SS/OC1B))
OFFSET: IC1.1 (OUT), IC1.2 (-IN), R22.2
OUTPUT: IC1.13 (-IN), IC1.14 (OUT), JP2.1, JP2.2, JP2.3, JP2.4, JP2.5, JP2.6
P0W: IC1.10 (+IN), U$1.12 (P0W)
P1A: C4.2, C10.1, U$1.10 (P1A), U$1.11 (P0A)
P3A: IC1.7 (OUT), U$1.1 (P3A), U$1.9 (P1W)
P3W: IC1.6 (-IN), U$1.2 (P3W), U$1.20 (P2A)
RAW: C3.1, R14.2, R15.2
SCK: J2.3 (SCK), U1.17 (PB5(SCK))
SCL: JP1.3, JP1.4, R25.2, U1.28 (PC5(ADC5/SCL)), U$1.5 (SCL)
SDA: JP1.1, JP1.2, R24.2, U1.27 (PC4(ADC4/SDA)), U$1.6 (SDA)
SIGNAL: C10.2, IC1.8 (OUT), IC1.9 (-IN), R23.2

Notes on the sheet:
R2R Digital to Analog Converter Stage
Sallen Key Lowpass Filter
Non inverting amplifier
Digital POT
Opamp supply decoupling caps
Voltage inverter ...

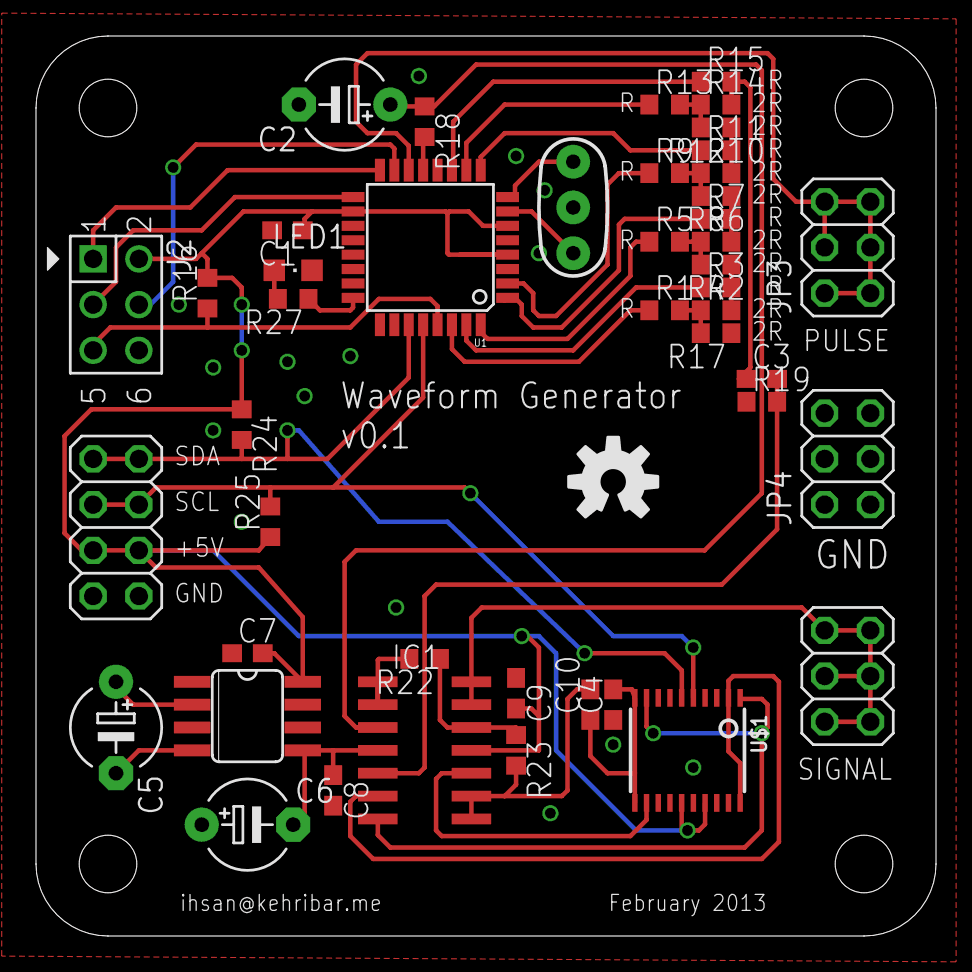
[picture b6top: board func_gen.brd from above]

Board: 2 copper layers, 50.0 x 50.0 mm, 47 parts (0 on the bottom side), 43 nets.

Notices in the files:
parts and their libraries:
SparkFun-DigitalIC_ihsan: Licensing: CC v3.0 Share-Alike You are welcome to use this library for commercial purposes.
microbuilder: This work is placed in the public domain, and may be freely used for commercial and non-commercial work with the following conditions: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
